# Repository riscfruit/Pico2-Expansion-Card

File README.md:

# FramePico2-Expansion-Card
An expansion card for Framework laptops and any other hardware, based on RP2354

### Gallery

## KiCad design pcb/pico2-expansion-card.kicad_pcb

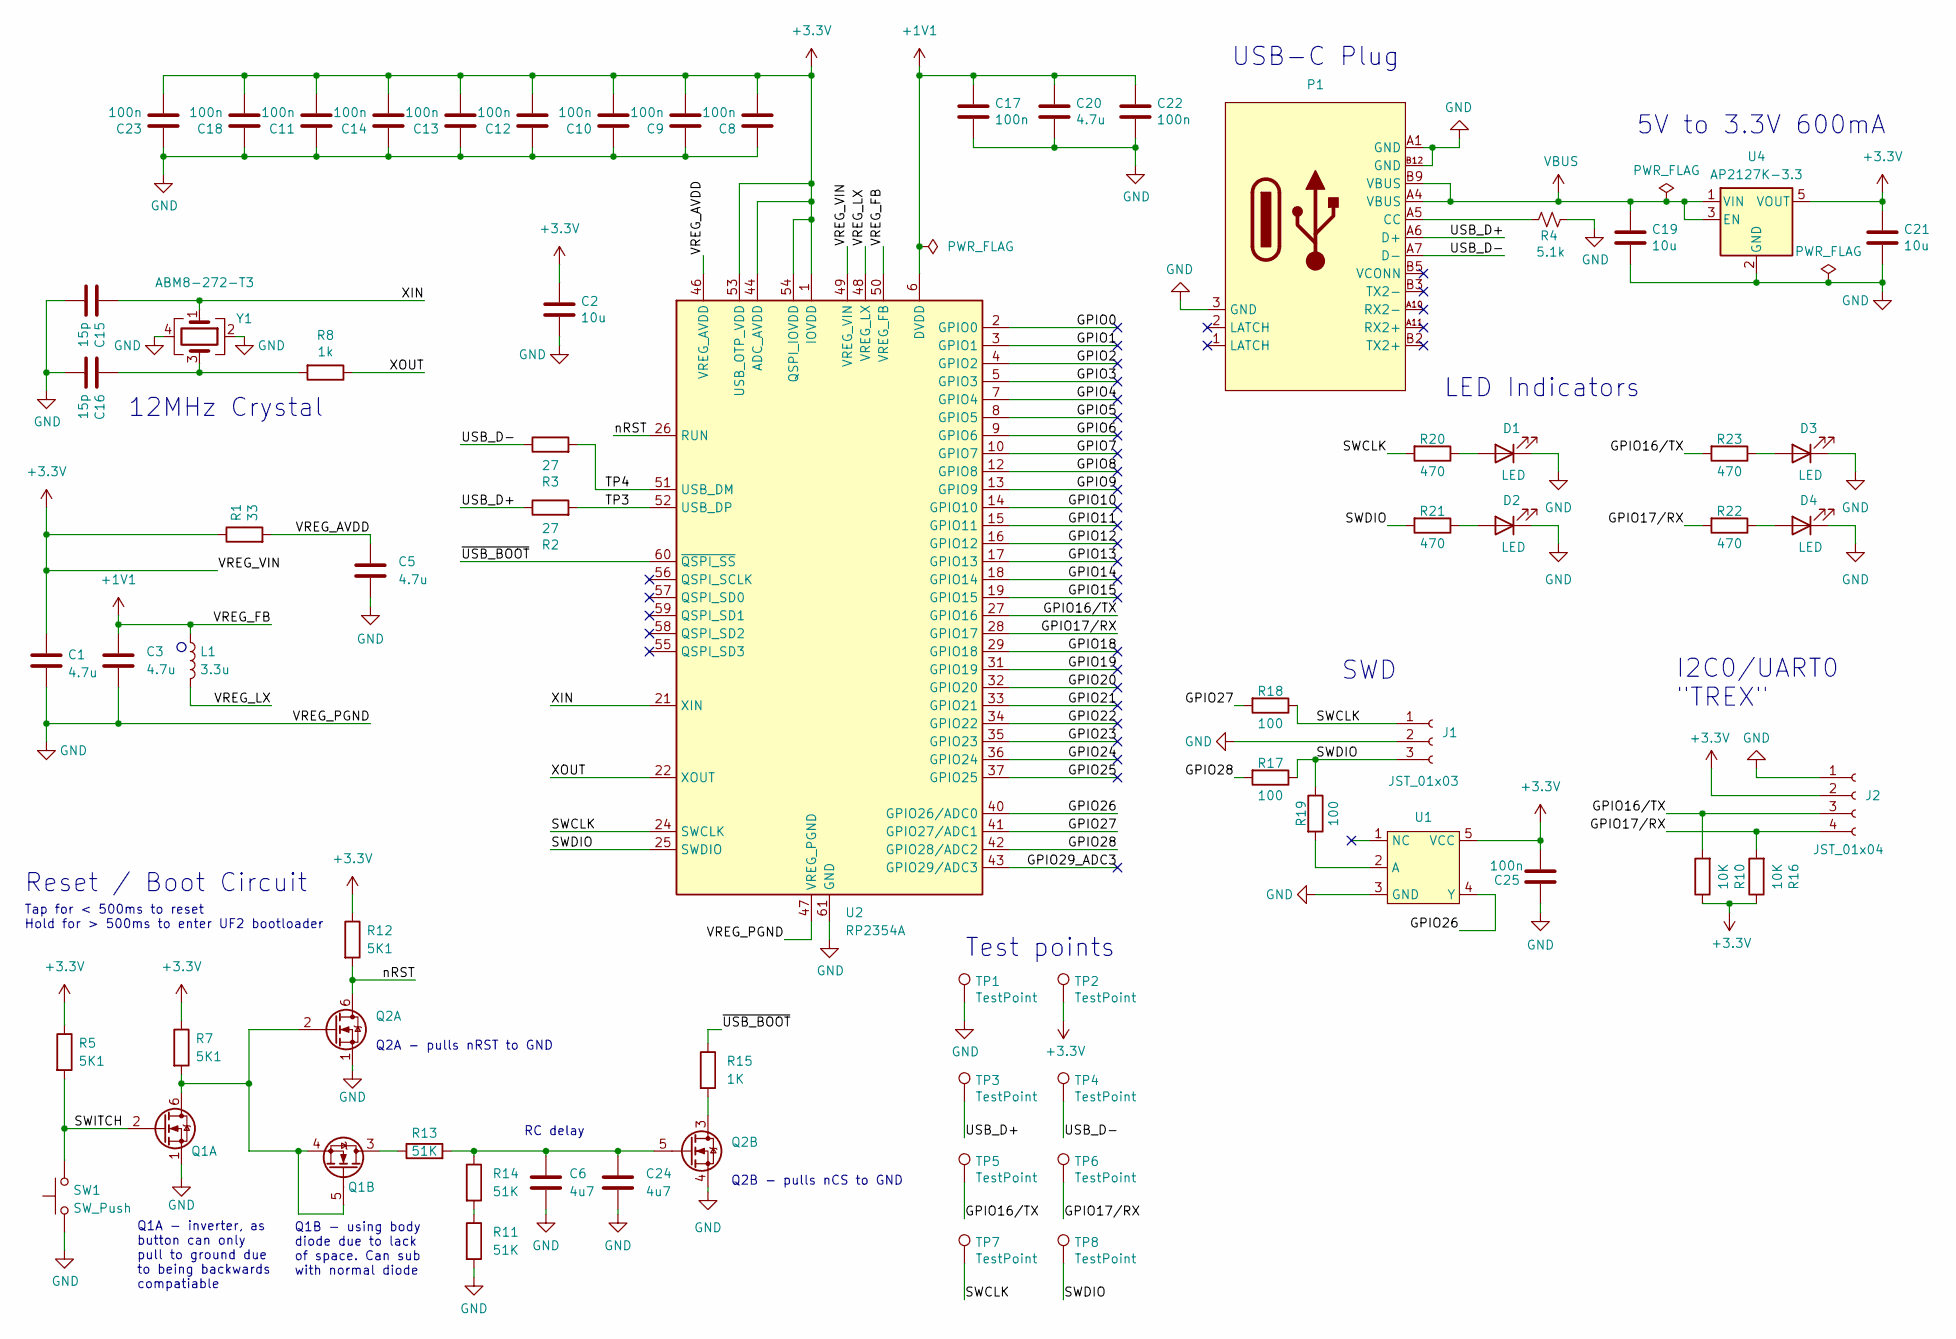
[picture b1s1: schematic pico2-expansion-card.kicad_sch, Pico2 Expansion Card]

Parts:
C1, C3: 4.7u; C_0402_1005Metric_small_pads
C2, C19, C21: 10u; C_0805_2012Metric
C5, C20: 4.7u; C_0402_1005Metric
C6, C24: 4u7; C_0402_1005Metric; MPN CL05A475MP5NRNC; JLC Basic Y
C8, C9, C10, C11, C12, C13, C14, C17, C18, C22, C23, C25: 100n; C_0402_1005Metric
C15, C16: 15p; C_0402_1005Metric
D1, D2, D3, D4: LED; LED_0402_1005Metric
J1: JST_01x03; JST_SH_SM03B-SRSS-TB_1x03-1MP_P1.00mm_Horizontal
J2: JST_01x04; JST_SH_SM04B-SRSS-TB_1x04-1MP_P1.00mm_Horizontal
L1: 3.3u; IND-SMD_L2.0-W1.6_AOTA-B201610S3R3-101-T
P1: USB-C-SMD_TYPE-C-31-G-10
Q1, Q2: EM6K6; SOT-563; MPN 2N7002V; JLC Basic N
R1: 33; R_0402_1005Metric
R2, R3: 27; R_0402_1005Metric
R4: 5.1k; R_0402_1005Metric
R5, R7, R12: 5K1; R_0402_1005Metric; MPN 0402WGF5101TCE; LCSC C25905
R8: 1k; R_0402_1005Metric
R10, R16: 10K; R_0402_1005Metric
R11, R13, R14: 51K; R_0402_1005Metric; MPN 0402WGF5102TCE; JLC Basic Y
R15: 1K; R_0402_1005Metric; MPN 0402WGF1001TCE; LCSC C11702
R17, R18, R19: 100; R_0402_1005Metric
R20, R21, R22, R23: 470; R_0402_1005Metric
SW1: SW_Push; BUTTON-SW-SMD_2P-TS24CA
TP1, TP2, TP3, TP4, TP5, TP6, TP7, TP8: TestPoint; TestPoint_Pad_1.0x1.0mm
U1: TECH PUBLIC TP74AUP1T17C5
U2: RP2354A; RP2350-QFN-60-1EP_7x7_P0.4mm_EP3.4x3.4mm_ThermalVias
U4: AP2127K-3.3; SOT-23-5
Y1: ABM8-272-T3; Crystal_SMD_3225-4Pin_3.2x2.5mm

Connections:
+1V1: C3.1, C17.1, C20.1, C22.1, L1.1, U2.6 (DVDD), U2.23 (DVDD), U2.39 (DVDD), U2.50 (VREG_FB)
+3.3V: C1.1, C2.1, C8.2, C9.2, C10.2, C11.2, C12.2, C13.2, C14.2, C18.2, C21.1, C23.2, J2.2, R1.1, R5.1, R7.1, R10.1, R12.1, R16.1, TP2.1 (1_1), U2.1 (IOVDD), U2.11 (IOVDD), U2.20 (IOVDD), U2.30 (IOVDD), U2.38 (IOVDD), U2.44 (ADC_AVDD), U2.45 (IOVDD), U2.49 (VREG_VIN), U2.53 (USB_OTP_VDD), U2.54 (QSPI_IOVDD), U4.5 (VOUT)
/GPIO0: U2.2 (GPIO0)
/GPIO1: U2.3 (GPIO1)
/GPIO2: U2.4 (GPIO2)
/GPIO3: U2.5 (GPIO3)
/GPIO4: U2.7 (GPIO4)
/GPIO5: U2.8 (GPIO5)
/GPIO6: U2.9 (GPIO6)
/GPIO7: U2.10 (GPIO7)
/GPIO8: U2.12 (GPIO8)
/GPIO9: U2.13 (GPIO9)
/GPIO10: U2.14 (GPIO10)
/GPIO11: U2.15 (GPIO11)
/GPIO12: U2.16 (GPIO12)
/GPIO13: U2.17 (GPIO13)
/GPIO14: U2.18 (GPIO14)
/GPIO15: U2.19 (GPIO15)
/GPIO16/TX: J2.3, R10.2, R23.2, TP5.1 (1_1), U2.27 (GPIO16)
/GPIO17/RX: J2.4, R16.2, R22.2, TP6.1 (1_1), U2.28 (GPIO17)
/GPIO18: U2.29 (GPIO18)
/GPIO19: U2.31 (GPIO19)
/GPIO20: U2.32 (GPIO20)
/GPIO21: U2.33 (GPIO21)
/GPIO22: U2.34 (GPIO22)
/GPIO23: U2.35 (GPIO23)
/GPIO24: U2.36 (GPIO24)
/GPIO25: U2.37 (GPIO25)
/GPIO26: U1.4 (Y), U2.40 (GPIO26/ADC0)
/GPIO27: R18.2, U2.41 (GPIO27/ADC1)
/GPIO28: R17.2, U2.42 (GPIO28/ADC2)
/GPIO29_ADC3: U2.43 (GPIO29/ADC3)
/SWCLK: J1.1, R18.1, R20.2, TP7.1 (1_1), U2.24 (SWCLK)
/SWDIO: J1.3, R17.1, R19.1, R21.2, TP8.1 (1_1), U2.25 (SWDIO)
/SWITCH: Q1.2 (G), R5.2, SW1.2
/TP3: R2.2, U2.52 (USB_DP)
/TP4: R3.2, U2.51 (USB_DM)
/USB_D+: P1.A6 (D+), R2.1, TP3.1 (1_1)
/USB_D-: P1.A7 (D-), R3.1, TP4.1 (1_1)
/VREG_AVDD: C5.1, R1.2, U2.46 (VREG_AVDD)
/VREG_LX: L1.2, U2.48 (VREG_LX)
/XIN: C15.1, U2.21 (XIN), Y1.1
/XOUT: R8.1, U2.22 (XOUT)
/nRST: Q2.6 (D), R12.2, U2.26 (RUN)
/~USB_BOOT: R15.1, U2.60 (~QSPI_SS)
GND: C1.2, C2.2, C3.2, C5.2, C6.2, C8.1, C9.1, C10.1, C11.1, C12.1, C13.1, C14.1, C15.2, C16.2, C17.2, C18.1, C19.2, C20.2, C21.2, C22.2, C23.1, C24.2, C25.1, D1.1 (K), D2.1 (K), D3.1 (K), D4.1 (K), J1.2, J2.1, P1.3 (GND), P1.A1 (GND), P1.B12 (GND), Q1.1 (S), Q2.1 (S), Q2.4 (S), R4.2, R11.2, SW1.1, TP1.1 (1_1), U1.3 (GND), U2.47 (VREG_PGND), U2.61 (GND), U4.2 (GND), Y1.2, Y1.4
unnamed: C16.1, R8.2, Y1.3
unnamed: D1.2 (A), R20.1
unnamed: D2.2 (A), R21.1
unnamed: D3.2 (A), R23.1
unnamed: D4.2 (A), R22.1
unnamed: P1.A5 (CC), R4.1
unnamed: Q1.4 (S), Q1.5 (G), Q1.6 (D), Q2.2 (G), R7.2
unnamed: Q1.3 (D), R13.1
unnamed: Q2.3 (D), R15.2
unnamed: C6.1, C24.1, Q2.5 (G), R13.2, R14.1
unnamed: R11.1, R14.2
unnamed: R19.2, U1.2 (A)
unnamed: C25.2, U1.5 (VCC)
VBUS: C19.1, P1.A4 (VBUS), P1.B9 (VBUS), U4.1 (VIN), U4.3 (EN)

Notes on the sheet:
Q2B - pulls nCS to GND
Tap for < 500ms to reset Hold for > 500ms to enter UF2 bootloader
LED Indicators
USB-C Plug
Q1B - using body diode due to lack of space. Can sub with normal diode
12MHz Crystal
Reset / Boot Circuit
Q1A - inverter, as button can only pull to ground due to being backwards compatiable
5V to 3.3V 600mA
I2C0/UART0 "TREX"
Test points
SWD
RC delay
Q2A - pulls nRST to GND

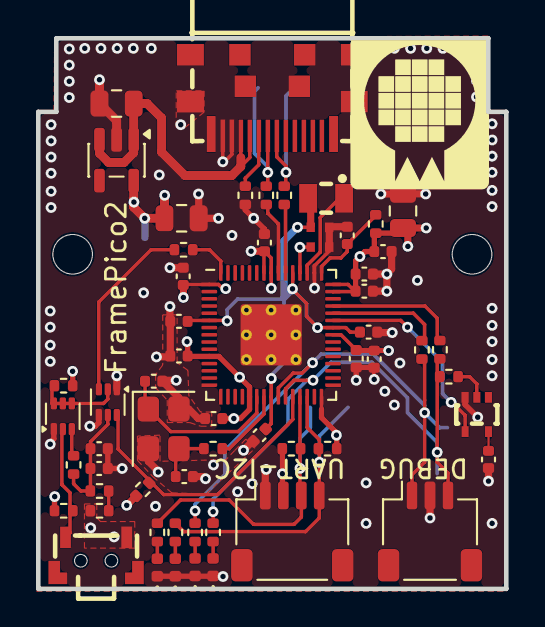
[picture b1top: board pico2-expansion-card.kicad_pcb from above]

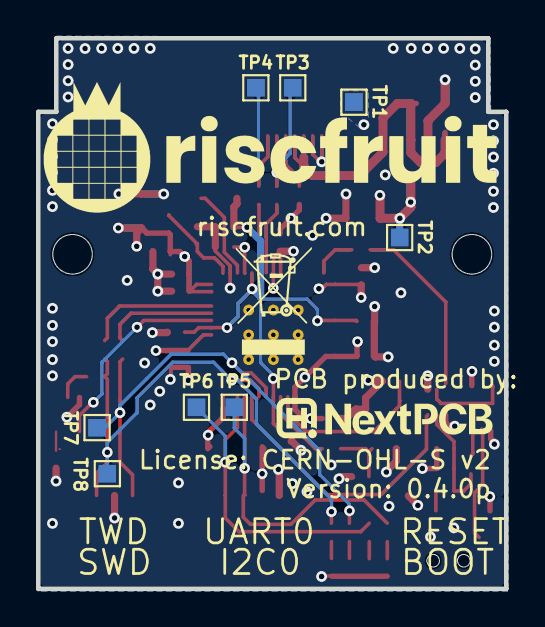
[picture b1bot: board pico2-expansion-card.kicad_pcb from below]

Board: 4 copper layers, 26.0 x 30.6 mm, 69 parts (8 on the bottom side), 35 nets.

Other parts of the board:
H1, H1#2: MountingHole; MountingHole_2.2mm_M2

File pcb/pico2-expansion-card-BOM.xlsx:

Reference | Qty | MPN | Manufacturer | Value | DNP | Exclude from BOM | Exclude from Board | Footprint | Datasheet
C1,C3 | 2 |  |  | 4.7u |  |  |  | Capacitor_SMD:C_0402_1005Metric_small_pads
C2,C19,C21 | 3 |  |  | 10u |  |  |  | Capacitor_SMD:C_0805_2012Metric
C5,C20 | 2 |  |  | 4.7u |  |  |  | Capacitor_SMD:C_0402_1005Metric
C6,C24 | 2 |  |  | 4u7 |  |  |  | Capacitor_SMD:C_0402_1005Metric
C8,C9,C10,C11,C12,C13,C14,C17,C18,C22,C23 | 11 |  |  | 100n |  |  |  | Capacitor_SMD:C_0402_1005Metric
C15,C16 | 2 |  |  | 15p |  |  |  | Capacitor_SMD:C_0402_1005Metric
J3 | 1 | 1.0-3P WT | SHOU HAN | Conn_01x03_Socket |  |  |  | Connector_JST:JST_SH_SM03B-SRSS-TB_1x03-1MP_P1.00mm_Horizontal
J4 | 1 | 1.0-4P WT | SHOU HAN | Conn_01x04_Socket |  |  |  | Connector_JST:JST_SH_SM04B-SRSS-TB_1x04-1MP_P1.00mm_Horizontal
L1 | 1 | AOTA-B201610S3R3-101-T | ABRACON | 3.3u |  |  |  | pico2parts:IND-SMD_L2.0-W1.6_AOTA-B201610S3R3-101-T
P1 | 1 | TYPE-C-31-G-10 | Korean Hroparts Elec |  |  |  |  | pico2parts:USB-C-SMD_TYPE-C-31-G-10
Q1,Q2 | 2 | EM6K6T2R | ROHM | EM6K6 |  |  |  | Package_TO_SOT_SMD:SOT-563 | http://www.gneic.com/product/datasheet/FDG6335N-1122853.pdf
R1 | 1 |  |  | 33 |  |  |  | Resistor_SMD:R_0402_1005Metric
R2,R3 | 2 |  |  | 27 |  |  |  | Resistor_SMD:R_0402_1005Metric
R4 | 1 |  |  | 5.1k |  |  |  | Resistor_SMD:R_0402_1005Metric
R5,R7,R12 | 3 |  |  | 5K1 |  |  |  | Resistor_SMD:R_0402_1005Metric
R8 | 1 |  |  | 1k |  |  |  | Resistor_SMD:R_0402_1005Metric
R11,R13,R14 | 3 |  |  | 51K |  |  |  | Resistor_SMD:R_0402_1005Metric
R15 | 1 |  |  | 1K |  |  |  | Resistor_SMD:R_0402_1005Metric
R6,R9 | 2 |  |  | 10K
SW1 | 1 | TS24CA |  | SW_Push |  |  |  | pico2parts:BUTTON-SW-SMD_2P-TS24CA
TP1,TP2,TP3,TP4 | 4 |  |  | TestPoint | DNP |  |  | TestPoint:TestPoint_Pad_D1.0mm
U2 | 1 | RP2354A | Raspberry Pi | RP2354A |  |  |  | pico2parts:RP2350-QFN-60-1EP_7x7_P0.4mm_EP3.4x3.4mm_ThermalVias | https://datasheets.raspberrypi.com/rp2350/rp2350-datasheet.pdf
U4 | 1 | AP2127K-3.3TRG1 | Diodes | AP2127K-3.3 |  |  |  | Package_TO_SOT_SMD:SOT-23-5 | https://www.diodes.com/assets/Datasheets/AP2127.pdf
Y1 | 1 | ABM8-272-T3 | ABRACON | ABM8-272-T3 |  |  |  | Crystal:Crystal_SMD_3225-4Pin_3.2x2.5mm

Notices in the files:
pcb/pico2-expansion-card.kicad_pcb:
License: CERN-OHL-S
License: CERN-OHL-S v2
